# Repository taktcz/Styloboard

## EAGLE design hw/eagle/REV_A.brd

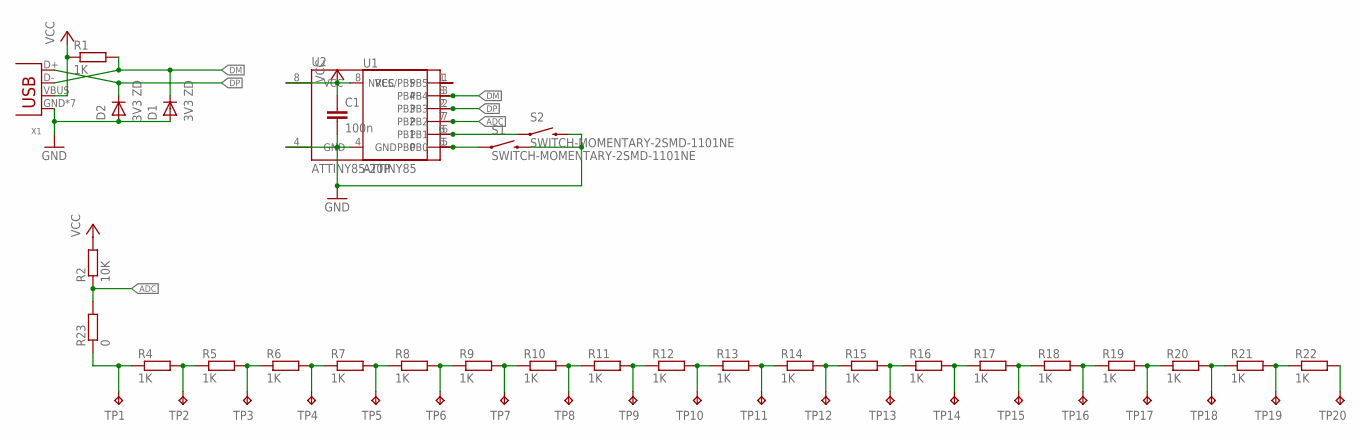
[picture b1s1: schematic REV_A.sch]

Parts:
C1: 100n; C0805K
D1, D2: 3V3 ZD; SOD80C
R1, R4, R5, R6, R7, R8, R9, R10, R11, R12, R13, R14, R15, R16, R17, R18, R19, R20, R21, R22: 1K; M0805
R2: 10K; M0805
R23: 0; M1206
S1, S2: SWITCH-MOMENTARY-2SMD-1101NE; TACTILE-SWITCH-1101NE
TP1, TP2, TP3, TP4, TP5, TP6, TP7, TP8, TP9, TP10, TP11, TP12, TP13, TP14, TP15, TP16, TP17, TP18, TP19, TP20: TPB1,27; B1,27
U1: ATTINY85
U2: ATTINY85-20P; PDIP08_300MIL
X1: USB-MB-S

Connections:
1: R4.1, R23.1, TP1.TP
2: R4.2, R5.1, TP2.TP
3: R5.2, R6.1, TP3.TP
4: R6.2, R7.1, TP4.TP
5: R7.2, R8.1, TP5.TP
6: R8.2, R9.1, TP6.TP
7: R9.2, R10.1, TP7.TP
8: R10.2, R11.1, TP8.TP
9: R11.2, R12.1, TP9.TP
10: R12.2, R13.1, TP10.TP
11: R13.2, R14.1, TP11.TP
12: R14.2, R15.1, TP12.TP
13: R15.2, R16.1, TP13.TP
14: R16.2, R17.1, TP14.TP
15: R17.2, R18.1, TP15.TP
16: R18.2, R19.1, TP16.TP
17: R19.2, R20.1, TP17.TP
18: R20.2, R21.1, TP18.TP
19: R21.2, R22.1, TP19.TP
20: R22.2, TP20.TP
ADC: R2.1, R23.2, U1.7 (PB2), U2.7 (PB2)
DM: D1.1 (K), R1.2, U1.3 (PB4), U2.3 (PB4), X1.D-
DP: D2.1 (K), U1.2 (PB3), U2.2 (PB3), X1.D+
GND: C1.2, D1.2 (A), D2.2 (A), S1.2, S2.2, U1.4 (GND), U2.4 (GND), X1.GND, X1.P$1 (GND), X1.P$2 (GND), X1.P$3 (GND), X1.P$4 (GND), X1.P$5 (GND), X1.P$6 (GND)
unnamed: U1.1 (PB5), U2.1 (NRES/PB5)
unnamed: S1.1, U1.5 (PB0), U2.5 (PB0)
unnamed: S2.1, U1.6 (PB1), U2.6 (PB1)
VCC: C1.1, R1.1, R2.2, U1.8 (VCC), U2.8 (VCC), X1.VBUS

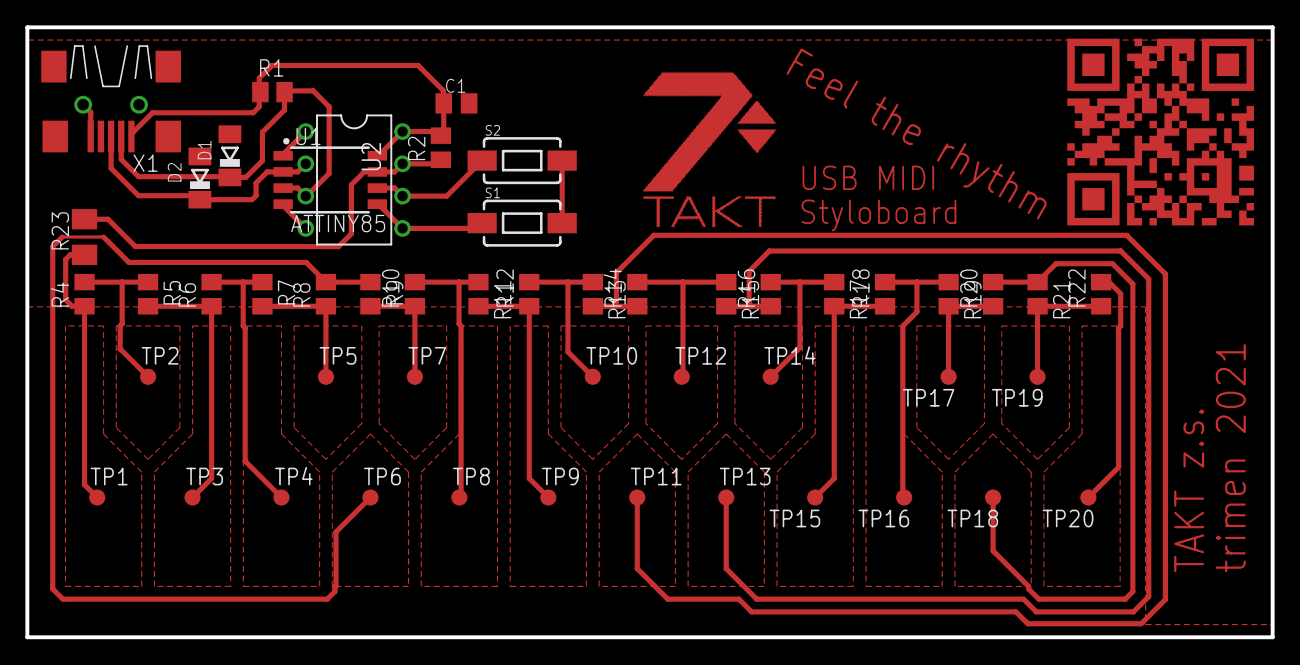
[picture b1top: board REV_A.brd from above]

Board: 2 copper layers, 98.0 x 48.0 mm, 50 parts (0 on the bottom side), 28 nets.

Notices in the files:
parts and their libraries:
SparkFun-Electromechanical: Licensing: Creative Commons ShareAlike 4.0 International - https://creativecommons.org/licenses/by-sa/4.0
